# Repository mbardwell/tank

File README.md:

# tank
3D printed, land-based tread vehicle.

# software
* GUI provided via Blynk app. Development in Arduino using Blynk API

# electrical
* Currently using individual boards to operate the tank. Future plans to build one PCB to do everything

# mechanical
* Files on Fusion360 server. No plan as of right now to open source these.

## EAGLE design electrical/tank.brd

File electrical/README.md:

# tank: electrical
* need to implement boost converter, DC motor drive, battery charger. Control handled by ESP8266 Feather Huzzah

* constraints: cost (max tbd), size (4" x 4" x 1"h)

## boost
* boost converter should take 8-12 V to above 20 V

## DC motor drive
* DC motor drive should be PWM or analog value controlled

## battery charger 
* battery charger should balance 6 Li-Po batteries via wall plug charger

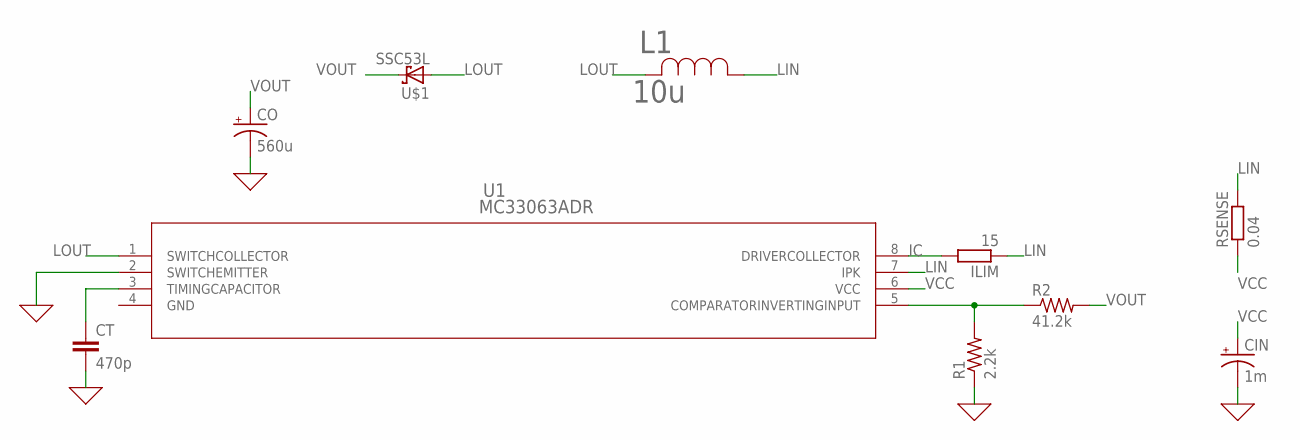
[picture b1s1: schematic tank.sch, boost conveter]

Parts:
CIN: 1m; E3,5-10; MANUFACTURER_PART_NUMBER ECA-1EM102
CO: 560u; E5-13; MANUFACTURER_PART_NUMBER EEU-FC1V561S
CT: 470p; C0402; MANUFACTURER_PART_NUMBER GRM155R71H471KA01D
ILIM: 15; R0603; MANUFACTURER_PART_NUMBER CSRN2010FK40L0CT-ND
L1: 10u; AIUR-06
R1: 2.2k; R0402; MANUFACTURER_PART_NUMBER ERJ-2RKF2201X
R2: 41.2k; R0805; MANUFACTURER_PART_NUMBER RC0805FR-0741K2L
RSENSE: 0.04; R2010; MANUFACTURER_PART_NUMBER CSRN2010FK40L0CT-ND
U1: MC33063ADR; D8
U$1: SSC53L; DO-214AB; MANUFACTURER_PART_NUMBER SSC53L-E3/57T

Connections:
0: CIN.-, CO.-, CT.2, R1.1, U1.2 (SWITCHEMITTER)
IC: ILIM.2, U1.8 (DRIVERCOLLECTOR)
LIN: ILIM.1, L1.1, RSENSE.2, U1.7 (IPK)
LOUT: L1.2, U1.1 (SWITCHCOLLECTOR), U$1.2 (A)
unnamed: R1.2, R2.1, U1.5 (COMPARATORINVERTINGINPUT)
unnamed: CT.1, U1.3 (TIMINGCAPACITOR)
VCC: CIN.+, RSENSE.1, U1.6 (VCC)
VOUT: CO.+, R2.2, U$1.1 (C)

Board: 2 copper layers, 11 parts (0 on the bottom side), 8 nets, no tracks yet.

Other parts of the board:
D1: DO-214AC

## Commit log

2018-06-15 start of tank esp code
2018-06-19 Started tank control class. Tried hosting a web server but the html/js/css files are not loading.
2018-07-06 PWM works, webpage works, need to adjust webpage to accept float values
2018-07-06 update ignore
2018-07-06 Added input field. Having issues saving values received to a var though
2018-07-11 minor updates
2018-07-11 Initilising blynk code
2018-07-11 Working joystick/button/slider app working
2018-07-11 Prepping for merge
2018-07-11 Combined multiple examples into esp_tank. Removed broken SPIFFS code base
2018-08-10 Adding electrical to git. Conglomerated software files
2018-08-10 Added electrical readme
2018-08-12 Reorganized
2018-08-18 NodeMCU program
2018-08-20 Initialised README
2018-08-20 Updated strategy in README
2018-08-20 Motion software initialised. Moves tank upon command with some bugs
2018-08-20 Added IC's and passives to schematic, library
2018-08-21 Added motion functions. Used them to drive tank around
2019-06-06 pre-linux
